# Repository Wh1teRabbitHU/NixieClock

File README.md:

# NixieClock

It's a custom design nixie clock, with code, schematics and board design.

## Design

### Nixie Clock - Controller

Source: ./design/NixieDisplayControllerV2

### Nixie Clock - Mother Board

Source: ./design/NixieDisplayMotherBoardV2

## Assembly

Under the folder assembly, you can find the generated files from kicad or if you want to order directly from JLCPB, then the compressed files ending with {Board_Name}_Gerber.zip can be used.

## Code

The mother board is controlled by an STM32L031 MCU and the code is created by using STMCube IDE. To upload the code, you just need to import the project and using an ST Link, you just need to upload directly to the chip. (No USART exposed)

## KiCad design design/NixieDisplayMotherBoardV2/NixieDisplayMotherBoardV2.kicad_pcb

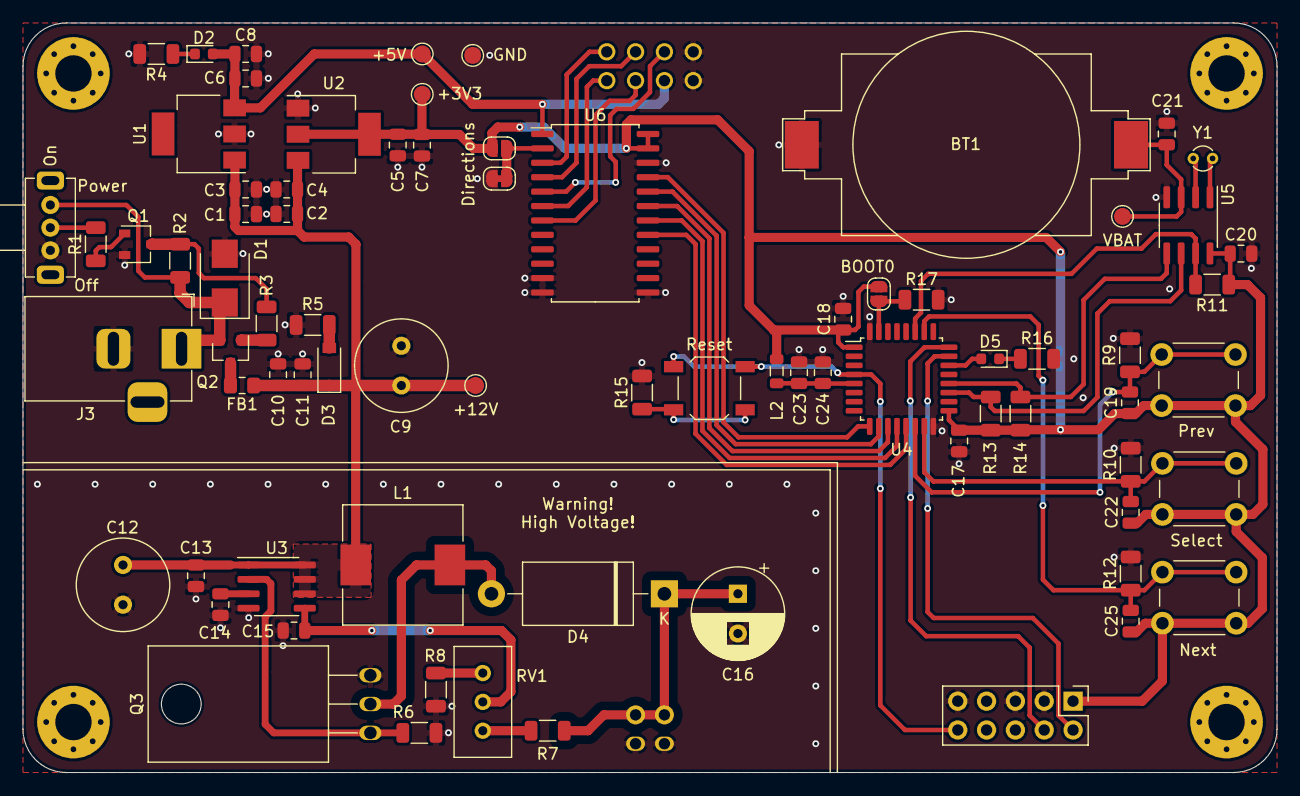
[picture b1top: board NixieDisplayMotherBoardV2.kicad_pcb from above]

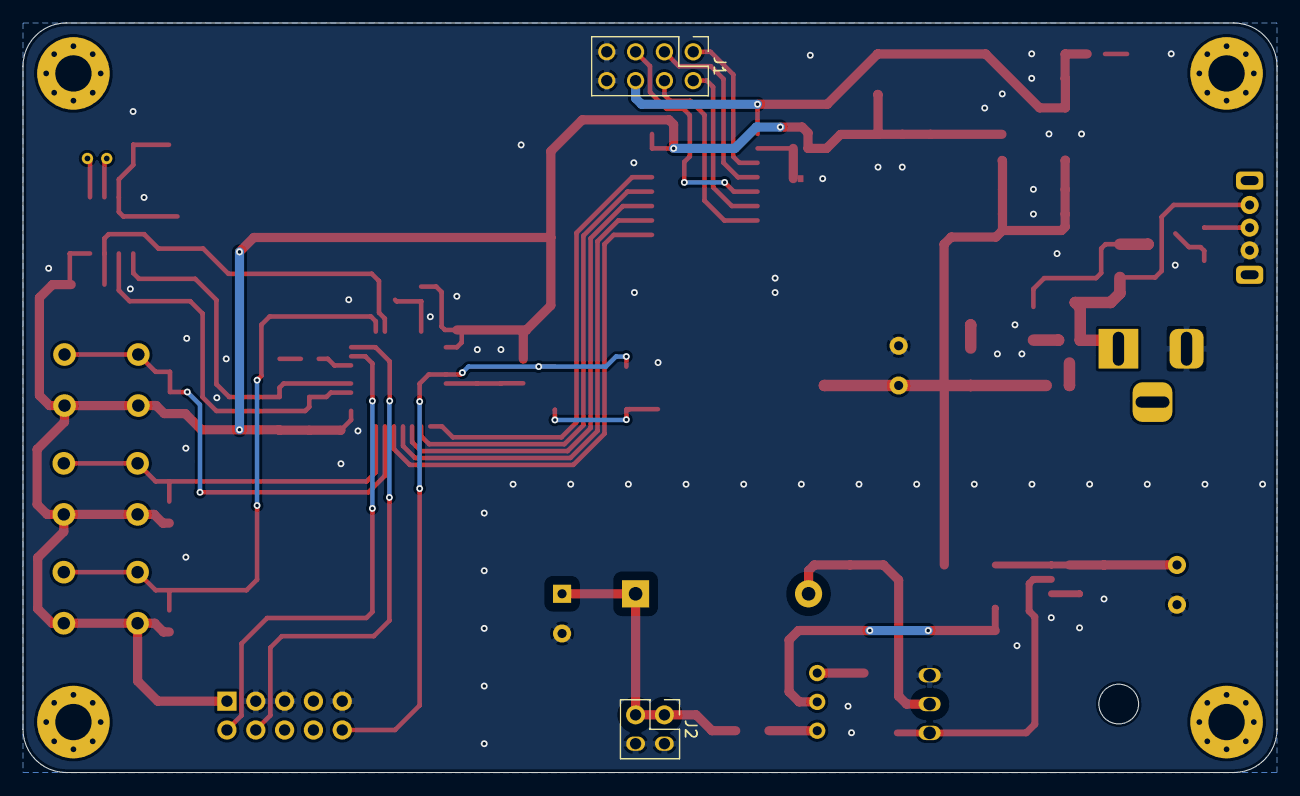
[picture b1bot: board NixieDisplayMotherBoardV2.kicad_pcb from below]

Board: 2 copper layers, 110.5 x 66.0 mm, 83 parts (2 on the bottom side), 47 nets.

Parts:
BT1: 3V Battery Cell; CR2032-BS-6-1
C1, C2, C23: 1uF; C_0805_2012Metric
C3, C4, C5, C6, C11, C13, C15, C17, C18, C19, C20, C21, C22, C24, C25: 0.1uF; C_0805_2012Metric
C7, C8, C10: 22uF; C_0805_2012Metric
C9, C12: 220uF; C_Radial_D8.0mm_H7.0mm_P3.50mm
C14: 1nF; C_0805_2012Metric
C16: 4.7uF 400V; CP_Radial_D8.0mm_P3.50mm
D1: SMBJ12CA-13-F; D_SMB
D2: Power Indicator; LED_0603_1608Metric
D3: 12V Zener; D_SOD-123
D4: HER504; D_DO-27_P15.24mm_Horizontal
D5: LED; LED_0603_1608Metric
FB1: FB 100; L_0805_2012Metric_Pad1.15x1.40mm_HandSolder
H1, H2, H3, H4: MountingHole; MountingHole_3.2mm_M3_Pad_Via
J1: Data Connector; PinHeader_2x04_P2.54mm_Vertical
J2: High Voltage Connector; PinHeader_2x02_P2.54mm_Vertical
J3: Barrel_Jack; BarrelJack_Horizontal
J4: SWD; PinHeader_2x05_P2.54mm_Vertical
JP1: BOOT0 EN; SolderJumper-2_P1.3mm_Open_RoundedPad1.0x1.5mm
JP2: Direction High; SolderJumper-2_P1.3mm_Open_RoundedPad1.0x1.5mm
JP3: Direction Low; SolderJumper-2_P1.3mm_Bridged_RoundedPad1.0x1.5mm
L1: 470uH 600mA; L_10.4x10.4_H4.8
L2: 39nH; L_0805_2012Metric
Q1: PMBT3904; SOT-23W
Q2: PMV50EPEAR; SOT-23
Q3: IRF840A; TO-220-3_Horizontal_TabDown
R1, R2, R9, R10, R11, R12, R15, R17: 10K; R_1206_3216Metric
R3, R4, R16: 1K; R_1206_3216Metric
R5: 100; R_1206_3216Metric
R6: 330; R_1206_3216Metric
R7: 750k; R_1206_3216Metric
R8: 4.7k; R_1206_3216Metric
R13, R14: 2.2K; R_1206_3216Metric
RV1: 3k; Potentiometer_Bourns_3296W_Vertical
SW1: SW_SPDT; Toggle-Switch-SK12D07VG4
SW2: Prev BTN; SW_PUSH_6mm_H9.5mm
SW3: Select BTN; SW_PUSH_6mm_H9.5mm
SW4: Next BTN; SW_PUSH_6mm_H9.5mm
SW5: Reset BTN; SW_SPST_TL3342
TP1: GND TP; TestPoint_Pad_D1.5mm
TP2: +3V3 TP; TestPoint_Pad_D1.5mm
TP3: +5V TP; TestPoint_Pad_D1.5mm
TP4: +12V TP; TestPoint_Pad_D1.5mm
TP5: VBAT TP; TestPoint_Pad_D1.5mm
U1: LM2940G-50-AA3-R; SOT-223
U2: AMS1117-3.3; SOT-223-3_TabPin2
U3: MC34063AD; SOIC-8_3.9x4.9mm_P1.27mm
U4: STM32L031K6Tx; LQFP-32_7x7mm_P0.8mm
U5: DS1338Z-33+; SOIC-8_3.9x4.9mm_P1.27mm
U6: 74LVC4245A; SOP-24_7.5x15.4mm_P1.27mm
Y1: 32.768KHz; Crystal_Round_D1.5mm_Vertical

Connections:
/+3V3: C5.1, C7.1, C17.1, C18.1, C19.1, C20.1, C22.1, C25.1, J4.1, JP1.2, JP2.1, L2.1, R11.1, R13.1, R14.1, SW2.2, SW3.2, SW4.2, TP2.1, U2.2, U4.1, U4.17, U5.8, U6.23, U6.24
/+5V: C6.1, C8.1, D2.2, J1.6, TP3.1, U1.3, U6.1
/+12V: C1.1, C2.1, C3.1, C4.1, C9.1, C10.1, C11.1, C12.1, C13.1, D3.1, FB1.1, L1.1, TP4.1, U1.1, U2.3, U3.1, U3.6, U3.7, U3.8
/+180V: C16.1, D4.1, J2.1, J2.3, R7.1
/DATA_CLK: J1.3, U6.4
/DATA_IN: J1.1, U6.3
/DATA_LATCH: J1.5, U6.5
/GND: BT1.2, C1.2, C2.2, C3.2, C4.2, C5.2, C6.2, C7.2, C8.2, C9.2, C10.2, C11.2, C12.2, C13.2, C14.2, C15.2, C16.2, C17.2, C18.2, C20.2, C21.2, C23.2, C24.2, D1.2, J1.7, J1.8, J2.2, J2.4, J3.2, J4.3, J4.5, J4.9, JP3.1, Q1.2, Q3.3, R4.2, R5.2, R6.2, R8.2, R9.2, R10.2, R12.2, R15.2, R16.2, R17.2, SW1.3, TP1.1, U1.2, U2.1, U3.4, U4.16, U4.32, U5.4, U6.11, U6.12, U6.13, U6.22
/VBAT: BT1.1, C21.1, TP5.1, U5.3
/uController/+3V3A: C23.1, C24.1, L2.2, U4.5
/uController/BOOT0: JP1.1, R17.1, U4.31
/uController/DATA_CLK_3V3: U4.10, U6.20
/uController/DATA_IN_3V3: U4.9, U6.21
/uController/DATA_LATCH_3V3: U4.11, U6.19
/uController/I2C1_SCL: R13.2, U4.19, U5.6
/uController/I2C1_SDA: R14.2, U4.20, U5.5
/uController/NEXT_BTN: C25.2, R12.1, SW4.1, U4.26
/uController/PREV_BTN: C19.2, R9.1, SW2.1, U4.14
/uController/RESET: J4.10, SW5.1, U4.4
/uController/RTC_INTERRUPT: R11.2, U4.27, U5.7
/uController/SELECT_BTN: C22.2, R10.1, SW3.1, U4.15
/uController/SIGNAL_LED: D5.2, U4.22
/uController/SWCLK: J4.4, U4.24
/uController/SWDIO: J4.2, U4.23
/uController/~DATA_CLR_3V3: U4.13, U6.17
/uController/~OUTPUT_EN_3V3: U4.12, U6.18
/~DATA_CLR: J1.4, U6.7
/~OUTPUT_EN: J1.2, U6.6
unnamed: C14.1, U3.3
unnamed: C15.1, RV1.2, U3.5
unnamed: D1.1, J3.1, Q2.2, R2.1, SW1.1
unnamed: D2.1, R4.1
unnamed: D3.2, R5.1
unnamed: D4.2, L1.2, Q3.2
unnamed: D5.1, R16.1
unnamed: FB1.2, Q2.3
unnamed: JP2.2, JP3.2, U6.2
unnamed: Q1.1, R1.1
unnamed: Q1.3, R2.2, R3.2
unnamed: Q2.1, R3.1
unnamed: Q3.1, R6.1, U3.2
unnamed: R1.2, SW1.2
unnamed: R7.2, RV1.3
unnamed: R8.1, RV1.1
unnamed: R15.1, SW5.2
unnamed: U5.1, Y1.2
unnamed: U5.2, Y1.1

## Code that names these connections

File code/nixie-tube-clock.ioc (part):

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Mcu.Name=STM32L031K(4-6)Ux
Mcu.Package=UFQFPN32
Mcu.UserName=STM32L031K6Ux
PA10.Mode=I2C
PA10.Signal=I2C1_SDA
PA12.GPIOParameters=GPIO_Label
PA12.GPIO_Label=SIGNAL_LED
PA12.Signal=GPIO_Output
PA13.Mode=Serial_Wire
PA13.Signal=SYS_SWDIO
PA14.Mode=Serial_Wire
PA14.Signal=SYS_SWCLK
PA3.GPIOParameters=GPIO_Label
PA3.GPIO_Label=CTRL_DATA_IN
PA3.Signal=GPIO_Output
PA4.GPIOParameters=GPIO_Label
PA4.GPIO_Label=CTRL_DATA_CLK
PA4.Signal=GPIO_Output
PA5.GPIOParameters=GPIO_Label
PA5.GPIO_Label=CTRL_DATA_LATCH
PA5.Signal=GPIO_Output
PA6.GPIOParameters=GPIO_Label
PA6.GPIO_Label=CTRL_OUT_EN
PA6.Signal=GPIO_Output
PA7.GPIOParameters=GPIO_Label
PA7.GPIO_Label=CTRL_DATA_CLR
PA7.Signal=GPIO_Output
PA9.Mode=I2C
PA9.Signal=I2C1_SCL
PB0.GPIOParameters=GPIO_Label
PB0.GPIO_Label=PREV_BTN
PB0.Signal=GPXTI0
PB1.GPIOParameters=GPIO_Label
PB1.GPIO_Label=SELECT_BTN
PB1.Signal=GPXTI1
PB3.GPIOParameters=GPIO_Label
PB3.GPIO_Label=NEXT_BTN
PB3.Signal=GPXTI3
PB4.GPIOParameters=GPIO_Label
PB4.GPIO_Label=RTC_INTERRUPT
PB4.Signal=GPXTI4
RCC.HSE_VALUE=8000000
RCC.SYSCLKFreq_VALUE=2097000
board=custom

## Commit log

2022-01-30 Initial code
2022-01-30 Adding design files
2022-01-30 Adding assembly files
2022-01-30 Adding some readme text
2022-01-30 Testing display
2022-01-30 Adding time display function
2022-01-30 Creating a driver to the DS1338Z RTC module
2022-01-30 Fixing I2C connection on the design
2022-01-30 Dirty solution to control the time to be able to start testing and using
